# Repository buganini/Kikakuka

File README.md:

# Kikakuka — KiCad Workspace, Panelization, Build Variants, Differ & FreeCAD PCB Bending and Assembly

Kikakuka (企画課, きかくか, Planning Section) creates a few more dimensions for KiCad:

* Workspace and project management
* Revision management
* Build variants
* Panelization
* FreeCAD integration for flexible PCB bending and multi-board assembly

## Quick links

* [Features](#features)
* [Workspace Manager](#workspace-manager)
* [Schematic and PCB Differ](#differ)
* [PCB Build Variants](#fabrication-planner---build-variants)
* [PCB Panelization](#fabrication-planner---panelizer)
* [FreekiCAD Integration](#freekicad-freecad-addon)
* [Flexible PCB Bending](#flexible-pcb-bending)
* [Kikakuka KiCad Library](#kikakuka-library)
* [Technical Background and Evolution](#technical-background-and-evolution)
* [Run from source on Linux/macOS](#run-from-source-linuxmacos)
* [Run from source on Windows](#run-from-source-windows)
* [CLI Usage](#cli-usage)
* [Gerber-to-KiCad Conversion](#reverse-engineering-notes-for-kicad-gerber)

# Features
* Kikakuka main program
    * Workspace Manager
        * Organize KiCad projects, FabPlans, FreeCAD documents, assemblies, and STEP files in `.kkkk` workspaces with relative paths and file descriptions
        * Open related schematic, PCB, and STEP files or launch Differ and FabPlan from the workspace
        * Inspect project-specific symbol and footprint libraries and convert their paths to `${KIPRJMOD}`-relative references
    * Instance Manager UI
        * Inspect same-user KiCad and FreeCAD processes and known file paths, with one row per FreeCAD document, the matched KiCad IPC socket basename, automatic mesh-event updates, manual reconciliation, and Go to actions
    * Differ
        * Highlight changed areas
        * [Schematic diff viewer](#schematics-differ)
        * [PCB diff viewer](#pcb-differ)
        * Git support
    * Fabrication Planner
        * Panelizer
            * Interactive arrangement with real-time preview
            * Freeform placement not limited to M×N grid configurations
            * Support for multiple different PCBs in a single panel
            * Automatic or manual tab creation
            * Automatic V-cut/mousebites selection
            * Enable [hole](#substrate-hole) creation in panel substrate for extruded parts
            * Load [KiKit multiboard files](https://yaqwsx.github.io/KiKit/v1.8/multiboard/) as multiple separate boards
            * No coding skills required
        * Build Variants
            * Single PCB without panelization can be done with frameless setting
            * Each PCB can have its own flag settings
        * Reproducible workflows
            * Create and edit fabrication plans interactively in the GUI.
            * Save configurations in a portable, JSON-based `.kkkk_fab` file.
            * Generate outputs from the saved plan using either the GUI or CLI.
    * Gerber handling
        * Available in the fabrication planner (panelizer)
        * Or direct conversion to .kicad_pcb
        * Compared with KiCad output
            * Better restoration of oval drill holes
            * Allow attaching BOM/CPL (converted to [reference-only footprints](resources/kikakuka-internal.pretty/Footprint.kicad_mod))
    * CLI - Convert saved fabrication plans (`.kkkk_fab`, or legacy `.kikit_pnl`) to KiCad files in one command

* FreekiCAD (FreeCAD Addon)
    * Reloadable KiCad PCB Object
        * Optional copper and solder-mask import, with outer copper, inner copper, and mask controlled independently
        * Solid [stiffeners](#flexible-pcb-stiffener) from annotated `F.Stiffener` and `B.Stiffener` user-layer areas
        * [Flex PCB bending](#flexible-pcb-bending) driven by bend lines and parameters defined in KiCad
        * [Automatic coupler-based PCB alignment](#coupler-based-pcb-alignment) using matching `CouplerFixed` and `CouplerMoving` footprints or an absolute `CouplerAt`, with coupler plane markers for inspection
        * A sketch is provided for real-time board outline editing in FreeCAD
        * Components moved in FreeCAD are synced to KiCad in real time
    * Reloadable STEP/STL Object
    * Import and export assembly manifests (`.kkkk_asm`)
    * CLI - Export saved assembly manifests (`.kkkk_asm`) to STEP or STL in one command

* KiCad Plugin/Library
    * Coupler footprints for [Automatic coupler-based PCB alignment](#coupler-based-pcb-alignment)
    * Plugin actions for previewing and hiding coupler helpers in the 3D Viewer
    * Populate scaled placeholder 3D models for footprints without a valid model, using `SizeX`, `SizeY`, and `SizeZ` properties
        - Tutorial Video

* CADhoc / Instance Manager
    * Seamless navigation among Kikakuka, KiCad, and FreeCAD across multiple instances and open documents

# Workspace Manager
The `.kkkk` file saves workspace information in JSON format.
Adding or dropping a `.kicad_pcb` or `.kicad_sch` records its sibling
`.kicad_pro` project entry, even when that project file has not been created
yet. A virtual project row omits the `.kicad_pro` suffix; an existing project
file keeps it. Rows list only PCB/schematic files that currently exist.
Opening a missing project row reports the missing project instead of launching
KiCad.

# Differ
## Schematics Differ

## PCB Differ

* A diff sample of [cynthion-hardware](https://github.com/greatscottgadgets/cynthion-hardware)

# Fabrication Planner
The `.kkkk_fab` file saves panelization and build-variants settings in JSON format, with PCB paths stored relative to the file's location. Legacy `.kikit_pnl` files can still be opened or added; newly saved fabrication plans use `.kkkk_fab`.

# Fabrication Planner - Build Variants
Example: [`samples/build_variant.kkkk_fab`](samples/build_variant.kkkk_fab) and [`samples/build_variant.kicad_pcb`](samples/build_variant.kicad_pcb).

Set `BUILDEXPR` in footprints' properties. This can be done quickly with `Symbol Fields Table` using the current sheet only scope. Remember to sync them to PCB afterward.

* Kikakuka extracts build flags from `BUILDEXPR`. Selected flags are interpreted as true, and vice versa.
* Footprints with the BUILDEXPR evaluated as false will be marked as DNP.
* Footprints with unset or empty BUILDEXPR will be kept as is.

## BUILDEXPR
A boolean expression with operators:
* `~` Not
* `&` And
* `|` Or

It can be as simple as a build name as shown in the image above or an expression like `(A | ~B) & C`.

Panelization with different build variants

Single PCB without panelization can be done with frameless setting

## Field Values Variants
`Field#Flag` or multiple flags like `Field#FlagA#FlagB` will set `Field` to the value where build flags contain all the flags.

`Field#Opt=A`, `Field#Opt=B` will be displayed as dropdown options.

# Fabrication Planner - Panelizer
## Tutorial Video

[![
Kikakuka/FabPlanner – Panelization](https://img.youtube.com/vi/40IOZ7cjGgk/0.jpg)](https://www.youtube.com/watch?v=40IOZ7cjGgk)

<!--
## Global Alignment

## Per-PCB Alignment

-->

## Substrate Hole

### 3D Output

<!--
## Tight Frame + Auto Tab + V-Cuts *or* Mousebites

### Output

### 3D Output

## Tight Frame + Auto Tab + V-Cuts *and* Mousebites

## Loose Frame + Auto Tab + Mousebites

### 3D Output

## Auto Tab
Tab position candidates are determined by the PCB edge and max_tab_spacing, prioritized by divided edge length (smaller first), and skipped if there is a nearby candidate (distance < max_tab_spacing/3) with higher priority.

In the image below with debug mode on, small red dots are tab position candidates, larger red circles are selected candidates, and the two rectangles represent the two half-bridge tabs.

## Manual Tab
Auto tab is off for PCB with manual tabs.
Drag inside the PCB for moving selected tab, drag outside the PCB for changing the direction for the selected tab.

-->

# FreekiCAD (FreeCAD Addon)
Requires **FreeCAD 1.0** or later, **KiCad 9.0** or later,
`psutil>=7.2.2`, `kicad-python>=0.8,<0.9`, and `shapely>=2.0.7`. FreeCAD Addon
Manager may not automatically install packages where its allowed-package list
excludes them; install them manually inside FreeCAD if necessary. Installing
FreekiCAD from Kikakuka's Integration tab installs all three Python packages.

> [!NOTE]
> FreeCAD installed through Snap is not supported. Snap confinement isolates
> the filesystem and local sockets, preventing FreekiCAD from connecting to
> KiCad's IPC endpoint. Selecting the Snap executable manually does not remove
> this isolation; use a non-Snap FreeCAD installation or the official AppImage.
>

FreekiCAD and Kikakuka discover each other on demand through local Unix sockets
or Windows named pipes. FreeCAD can manage KiCad
instances without the Workspace Manager running. No board, assembly, or usage
data is sent to third parties.

When opening a FreeCAD file, Kikakuka first looks for an already open document
or reuses a responding FreeCAD instance; see
[CADhoc](cadhoc/README.md) for details.

KiCad `.kicad_pcb` boards and STEP models remain external files referenced by
path. When saved as `.FCStd`, the FreeCAD document caches their generated
objects and geometry, but the links remain reloadable from the source files. A
`.kkkk_asm` manifest stores source paths, settings, placements, and an optional
structured 3D viewport camera; it never contains cached objects or geometry.
Source paths are stored relative to the manifest whenever possible and resolved
from its directory on import, when every external source is loaded fresh. The
camera is restored field by field in FreeCAD's GUI, skipping unsupported or
invalid fields, and ignored by headless STEP/STL export.
`AutoReload` is enabled by default on both object types, so changing either
source file reloads its linked FreeCAD object. The option can be disabled
independently for each object.

> [!TIP]
> You can use Kikakuka's **Integration** tab to install, update, or uninstall the
> bundled KiCad plugin, KiCad library, and FreekiCAD addon. Close all instances
> of the affected application before using an install or uninstall button.
> Release builds already contain the addon packages. When running Kikakuka
> from source, generate them first with
> `python3 build-tools/build_addon_archives.py` (or
> `make archive-zips`); the GUI loads the resulting runtime packages from
> `build/addons/`.

For a standalone FreekiCAD deployment without Kikakuka, follow the
[FreekiCAD manual installation instructions](FreekiCAD/README.md#manual-installation).

* Activate `Preferences -> Plugins -> Enable KiCad API`. Kikakuka or FreekiCAD can reuse a running matching KiCad editor or start one on demand.
* FreekiCAD (FreeCAD Addon)
    * Add PCB
        * Drag and drop / Open / Import
            * Drag a `.kicad_pcb` file into FreeCAD, or use FreeCAD's Open or Import command; switching workbenches is not required.
        * FreekiCAD menu
            * Switch to the `FreekiCAD` workbench.
            * Menubar -> FreekiCAD -> Add KiCad PCB.
        * All of these entry points create the same linked PCB object.
        * The selected `.kicad_pcb` remains an external file and is represented by a linked `PcbObject`. Its `AutoReload` property defaults to enabled.
    * Add STEP
        * Menubar -> FreekiCAD -> Add STEP
        * The selected STEP model remains an external file. Its `AutoReload` property defaults to enabled, and its Placement is preserved when the source file is manually or automatically reloaded.
    * Position and assemble linked objects
        * Linked objects work with the `Assembly` and `Manipulator` workbenches, as well as FreeCAD's built-in transform tool.
        * FreeCAD Assembly can place `PcbObject` Links, but currently cannot resolve their child component or connector faces for joints. Use the Manipulator workbench to align those faces.
    * Reload PCB
        * Right-click on the board object -> Reload KiCad PCB
    * Export or import an assembly manifest
        * Use FreeCAD's standard Export command to write `.kkkk_asm`, or its Import command to read `.kkkk_asm`; select `FreekiCAD Assembly (*.kkkk_asm)` as the file type.
        * The JSON stores each external PCB or STEP source path, editable FreekiCAD settings, its placement, and—when exported from the GUI—the active 3D viewport camera. It contains no cached objects or generated geometry, and every external source is loaded fresh during import. Export prefers paths relative to the manifest and falls back to absolute paths only when necessary; relative paths are resolved from the manifest's directory. FreeCAD regenerates object names and labels during import. GUI import restores each available camera field independently after recomputation and skips fields that are invalid or unsupported; headless STEP/STL export ignores the camera.
        * Selecting an original `PcbObject` or `StepObject` exports its own Placement. Selecting one or more `App::Link` instances exports each linked source at that instance's final global placement. Selecting an `Assembly::AssemblyObject` recursively expands its direct and nested Links, including multiple instances of the same source.
        * Assembly and Link exports are flattened placement snapshots; `.kkkk_asm` does not store Links, joints, constraints, remaining degrees of freedom, or the Assembly hierarchy. A linked PCB snapshot is exported with `SnapToCoupler` disabled in the manifest so coupler alignment cannot overwrite its solved Assembly placement; the source `PcbObject` in the current FreeCAD document is not modified.
        * When original PCB source objects are selected directly, Placement is omitted for a `CouplerMoving` board if the same export contains its matching `CouplerFixed` board; coupler alignment recalculates that placement after import.
        * Headless STEP export: `freecadcmd scripts/kkkk_export.py input.kkkk_asm output.step`; the input may also be a single `.kicad_pcb`. See [Headless STEP and STL Export](FreekiCAD/README.md#headless-step-and-stl-export) for platform-specific paths and requirements.
    * Edit Board Shape
        * Expand the object's children.
        * Open the sketch with the `_Outline` suffix.
    * Inspect Copper Layers
        * FreekiCAD imports tracks, filled zones, pads, vias, and copper-layer graphics as separate `F.Cu`, `In*.Cu`, and `B.Cu` child objects.
        * `ImportOuterCopper` independently controls `F.Cu` and `B.Cu`; `ImportInnerCopper` controls `In*.Cu`. Both default to off.
        * Inner layers use their physical stackup Z and are normally hidden by the board body; hide the board or make it transparent to inspect them.
        * Copper is rendered as one unioned zero-thickness face per layer, eliminating overlap between tracks, pads, vias, and zones. Each face retains its physical stackup Z, so inner layers follow the correct bend radius.
        * The substrate remains one body. Imported outer copper reserves its physical stackup thickness at the body boundary; inner copper does not create expensive internal body cavities. Finished board thickness and component/coupler Z never change.
    * Inspect Solder Mask
        * `ImportSolderMask` imports translucent `F.Mask` and `B.Mask` child objects, with pad/via openings computed by KiCad plus explicit mask-layer graphics. It defaults to off.
        * The resulting F/B mask-opening geometry is also subtracted from stiffener solids on the matching side.
        * With mask import enabled, the board body uses the configured dielectric stackup colors and KiCad opacity, or white with KiCad's default board-body opacity when no color is available. Mask opacity likewise follows its KiCad stackup color. Both display opacities are scaled to 70% in FreeCAD. With mask import disabled, the original opaque board color is preserved.
        * Mask is a zero-thickness face at the finished outer surface. Imported mask reserves its physical outer stackup thickness in the single substrate body; when mask import is disabled, the body fills that thickness.
    * Inspect Silkscreen
        * `ImportSilkscreen` imports board- and footprint-level graphics, references, values, fields, and free text from `F.SilkS` and `B.SilkS`. It defaults to off.
        * Silkscreen is a zero-thickness face on the finished board surface. A Coin3D polygon offset resolves viewport z-fighting without moving the geometry, so measurements, bounds, and exports retain the exact finished dimensions.
    * [Flexible PCB Stiffener](#flexible-pcb-stiffener)
        * Import annotated stiffener solids automatically from `F.Stiffener` and `B.Stiffener` user layers.
    * [Coupler-Based PCB Alignment](#coupler-based-pcb-alignment)
        * Place a `CouplerFixed` footprint on the reference PCB and a `CouplerMoving` footprint on the PCB to be aligned. Couplers are matched by their KiCad reference.
        * Alternatively, place one `CouplerAt` on a PCB to align it with a virtual `CouplerFixed` at the absolute FreeCAD world coordinates given by its `TargetX`, `TargetY`, and `TargetZ` properties. All three default to `0 mm`. Usually place `CouplerAt` on B.Cu so the PCB bottom surface is positioned at `TargetZ`; use F.Cu only when the top surface should be the reference. A PCB may contain only one positioning source: one `CouplerMoving` or one `CouplerAt`.
        * After any linked PCB reloads, positioning is recalculated for every linked PCB in dependency order. A concurrently reloading PCB is skipped until its fresh poses and bent markers are available; its completion triggers another full pass. A PCB with `SnapToCoupler` enabled (the default) is moved as a whole so that its moving coupler plane meets the matching fixed coupler plane face-to-face; disabling it excludes that PCB from automatic positioning. Alignment uses each plane's position after flex-PCB bending. Each coupler is also available as a child object in FreeCAD; its plane marker is hidden by default and can be shown for inspection.
        * FreekiCAD checks the saved coupler list against KiCad's live document every second, including unsaved position, side, rotation, `Z`, `Offset`, `Tilt`, and `CouplerAt` target edits. A changed pose updates its marker and recalculates linked-board positioning. The coupler child object's footprint position and local-plane properties are editable in FreeCAD; edits update the marker and linked-board positioning immediately and are written back to the live KiCad footprint. `Y` is shown using FreeCAD's axis convention. Older footprints without an `Offset` field load as `0 mm`; editing `Offset` in FreeCAD creates the missing hidden KiCad field automatically. Adding, removing, or changing the identity of couplers takes effect on the next PCB reload, which rebuilds the saved list.
        * The [`kicad-addon/library`](kicad-addon/library) directory provides [`CouplerFixed`](kicad-addon/library/footprints/Kikakuka.pretty/CouplerFixed.kicad_mod), [`CouplerMoving`](kicad-addon/library/footprints/Kikakuka.pretty/CouplerMoving.kicad_mod), and [`CouplerAt`](kicad-addon/library/footprints/Kikakuka.pretty/CouplerAt.kicad_mod).
        * Alignment example boards: [`assembly-power.kicad_pcb`](samples/assembly-power.kicad_pcb), [`assembly-mcu.kicad_pcb`](samples/assembly-mcu.kicad_pcb), [`assembly-led.kicad_pcb`](samples/assembly-led.kicad_pcb), and [`assembly-mezzanine.kicad_pcb`](samples/assembly-mezzanine.kicad_pcb).
        * The coupler plane is defined by the footprint position, side, rotation, and these custom footprint properties:
            * `CouplerFixed` and `CouplerMoving` use `Z` to move the plane origin along the PCB surface normal. It defaults to `0 mm`; the origin starts at the PCB surface, including the board thickness on F.Cu, and the direction is reversed on B.Cu.
            * `Offset` moves the plane origin on the PCB surface in the direction indicated by the footprint triangle. It defaults to `0 mm`. `Z` and `Offset` accept values without a unit as millimetres and support `mm`, `cm`, `in`, `mil` (`0.001 in`), and `um`.
            * `Tilt` tilts the plane around the footprint's local X axis. It is specified in degrees and defaults to `0`.
            * `CouplerAt` uses `TargetX`, `TargetY`, and `TargetZ` as its absolute FreeCAD world target and does not have a local `Z` property. The target properties default to `0 mm`; the same length units are supported. B.Cu is recommended for the usual bottom-surface placement at `TargetZ`; use F.Cu only to reference the top surface.
        * Placement applies the footprint position and rotation, then `Offset`, `Z`, and `Tilt`. `Tilt` rotates around the footprint's local X axis at the offset origin; it does not redirect either displacement. The footprint's normal KiCad rotation supplies the rotation around its local Z axis.
    * [Flex PCB Bending](#flexible-pcb-bending)
        * Name a KiCad graphical layer `FreekiCAD` (case-insensitive) and draw bend lines on it as line segments.
        * Panel export maps every source PCB's `FreekiCAD` drawings to one collision-free User layer and preserves the `freekicad` layer name, even when source boards use different `User.x` layers.
        * Add bend parameters as text on the same `FreekiCAD` layer near a bend line endpoint, for example `a=-70 r=0.5` or `a=-70 s=0.61`.
            * The text anchor must be within `0.1 mm` of a bend line endpoint.
            * `a` is bend angle in degrees.
            * `r` is bend radius. `s` is the full bend span and is used to derive `r` when `r` is omitted, using the board thickness from stackup.
            * Both lengths accept `mm`, `cm`, `um` (also `µm`/`μm`), `in`, and `mil`; omitted units mean mm. Unit suffixes are case-insensitive. Unsupported units are rejected.
            * Parameters may appear in any order, with whitespace around `=` and before units: `r = 5 mm a = 60` is equivalent to `a=60 r=5mm`. If both `r` and `s` are present, `r` takes precedence.
        * After loading the board in FreeCAD, each bend line appears as a child object with `Angle`, `Radius`, and `Active` properties.
        * The linked PCB object also has an `EnableBending` property to toggle the deformation on or off.
        * Imported copper and solder mask are cut with the same board pieces. Rigid display faces follow each piece, while faces in a bend band are rebuilt with the wedge's curved point mapping.
        * If no bend text is provided, the bend line still loads and can be configured directly in FreeCAD.

## Coupler-Based PCB Alignment

### Tutorial Video

### Positioning Arguments

### Coupler Pair

### Changing Z and Tilt

Coupler plane markers are available as child objects in FreeCAD and are hidden by default.

## Flexible PCB Stiffener

Rename KiCad user layers to `F.Stiffener` and/or `B.Stiffener`
(case-insensitive). Each closed rectangle, circle, polygon, or connected
line/arc outline is imported automatically as one stiffener area; the KiCad
display fill may be on or off.
Put one text annotation inside each area and separate properties with `/` or
newlines:

```text
Name=Tail reinforcement
Material=Polyimide
Color=#C87518
Opacity=0.65
Thickness=25 um
```

`Material` and `Thickness` are required. `Name`, `Color`, and `Opacity` are
optional and property names are case-insensitive. A non-empty `Name` becomes
the suffix of the FreeCAD child name and label (`F_Stiffener_<Name>` or
`B_Stiffener_<Name>`) and is included in bend-overlap warnings. Thickness
accepts `mm`, `cm`, `in`, `mil` (`0.001 in`), and `um`; a unitless value is
interpreted as millimetres.

Invalid annotations, annotations outside an area, and areas with multiple
annotations are reported as errors and skipped. Unannotated areas are skipped
with a warning.

| Material | Default color | Default opacity |
| --- | --- | ---: |
| `FR4` | `#C8B45A` | `0.90` |
| `Polyimide` | `#C87518` | `0.65` |
| `Stainless_Steel` | `#A7ADB4` | `1.00` |
| `3M468` | `#F2E3BD` | `0.28` |
| `tesa8854` | `#EEE8D8` | `0.45` |
| `3M9077` | `#DDE8EE` | `0.30` |

Other material names are accepted with a warning. When `Color` or `Opacity`
is omitted for an unlisted material, the corresponding `Polyimide` default is
used.

Front stiffeners extend outward from the front silkscreen plane; back
stiffeners extend outward from the back silkscreen plane. They remain rigid
during flex bending. Pad, via, and explicit mask-graphic openings on `F.Mask`
are cut through front stiffeners; `B.Mask` openings are cut through back
stiffeners. This happens even when `ImportSolderMask` is disabled. If a
stiffener overlaps the full bend band, FreekiCAD prints a warning containing
the stiffener name, bend name, and overlap area.

Stiffener thickness is additive outside the finished PCB and is never counted
in or subtracted from the board body.

## Flexible PCB Bending
### Tutorial Video

Manual bending checks are currently done with these sample boards:

* [`samples/fpc.kicad_pcb`](samples/fpc.kicad_pcb)
* [`samples/maze.kicad_pcb`](samples/maze.kicad_pcb)
* [`samples/maze_radius.kicad_pcb`](samples/maze_radius.kicad_pcb)

<!--

-->

For the implementation details of the bending pipeline, see [`FreekiCAD/ARCHITECTURE.md`](FreekiCAD/ARCHITECTURE.md).

### Bending + Assembly

# Kikakuka Library
The KiCad library is stored under [`kicad-addon/library`](kicad-addon/library).
You can install it from Kikakuka's **Integration** tab. For a manual installation,
add [`kicad-addon/library/footprints/Kikakuka.pretty`](kicad-addon/library/footprints/Kikakuka.pretty)
to KiCad's footprint library table (for example, as `Kikakuka`). Its
[`Kikakuka.3dshapes`](kicad-addon/library/3dmodels/Kikakuka.3dshapes) directory
contains the unit-cube placeholder and optional coupler helper models.

* [`Variable`](kicad-addon/library/footprints/Kikakuka.pretty/Variable.kicad_mod) displays its `Value` on the board. In the Kikakuka Fabrication Planner, use build-variant fields such as `Value#Flag` or `Value#Option=Choice` to show a value selected by the active build flags or options.
* [`StringTemplate`](kicad-addon/library/footprints/Kikakuka.pretty/StringTemplate.kicad_mod) formats its `Value` during Kikakuka Fabrication Planner export. Braced placeholders are replaced with matching footprint properties or build options after build-variant fields have been applied.
* [`CouplerFixed`](kicad-addon/library/footprints/Kikakuka.pretty/CouplerFixed.kicad_mod) and [`CouplerMoving`](kicad-addon/library/footprints/Kikakuka.pretty/CouplerMoving.kicad_mod) define matching planes for [coupler-based PCB alignment](#coupler-based-pcb-alignment). Give a pair the same reference and use their `Z`, `Offset`, and `Tilt` properties as needed.
* [`CouplerAt`](kicad-addon/library/footprints/Kikakuka.pretty/CouplerAt.kicad_mod) aligns its PCB to absolute FreeCAD world `TargetX`, `TargetY`, and `TargetZ` coordinates, all defaulting to zero. Place it on B.Cu for the usual behavior, where the PCB bottom surface is positioned at `TargetZ`; use F.Cu only to reference the top surface.

For coupler length properties (`Z`, `Offset`, `TargetX`, `TargetY`, and `TargetZ`), unitless values are millimetres; supported suffixes are `mm`, `cm`, `in`, `mil`, and `um`/`µm`. `Tilt` is in degrees and may optionally use `deg` or `°`.

All three coupler footprints use the `Unspecified` type, placing their helper models under **Virtual Models** in KiCad's 3D Viewer.

The separate Kikakuka Tools IPC plugin provides **Coupler 3D Viewer** and **Hide Couplers** actions. Coupler 3D Viewer applies each coupler's `Z`, `Tilt`, and `Offset` to its helper model and opens KiCad's 3D Viewer; Hide Couplers marks these models hidden without removing them and also opens the Viewer. **Populate Placeholder 3D Models** likewise opens the Viewer after populating models. To omit couplers from STEP export, enable **Ignore 'Unspecified' components**.

# Technical Background and Evolution
Kikakuka is mainly built on top of [KiKit](https://github.com/yaqwsx/KiKit), [Shapely](https://github.com/shapely/shapely), modified [pcb-tools](https://github.com/curtacircuitos/pcb-tools), [OpenCV](https://github.com/opencv/opencv-python), [pypdfium2](https://github.com/pypdfium2-team/pypdfium2) and [PUI](https://github.com/buganini/PUI).

Its FreeCAD integration is inspired by [KiCadStepUp](https://github.com/easyw/kicadStepUpMod) and [KiConnect](https://codeberg.org/kiconnect/KiConnect).

Kikakuka, formerly Kikit-UI, began as an interactive GUI for KiKit and later expanded to include a workspace manager. File-to-instance tracking was introduced to make navigation from the workspace manager to KiCad reliable, with the workspace manager initially serving as the central orchestrator. After FreekiCAD was introduced, that mechanism evolved into CADhoc, a mesh of peer nodes running in Kikakuka and FreekiCAD without a permanent central orchestrator. The mesh also includes a client-only node in the KiCad add-on. CADhoc maintains a shared view of KiCad and FreeCAD instances and their open documents, so navigation no longer depends on the workspace manager.

# Run from source (Linux/macOS)
Make sure your python can import `pcbnew`
```
> python3 -c "import pcbnew; print(pcbnew._pcbnew)"
<module '_pcbnew' from '/usr/lib/python3/dist-packages/_pcbnew.so'>
```
On macOS, I have to use the python interpreter bundled with KiCAD
```
PYTHON=/Applications/KiCad/KiCad.app/Contents/Frameworks/Python.framework/Versions/Current/bin/python3
```

On Linux, you should be able to just use the your default python3
```
PYTHON=python3
```

Create a virtual environment and install dependencies
```
${PYTHON} -m venv --system-site-packages env
./env/bin/pip3 install -r requirements.txt
```

On Debian/Ubuntu, PySide6's X11 platform plugin also needs these system libraries:
```
sudo apt install libxcb-cursor0 libxkbcommon-x11-0 libxcb-icccm4 libxcb-image0 libxcb-keysyms1 libxcb-render-util0 libxcb-xkb1
```

Kikakuka uses `opencv-python-headless` for image processing and PySide6 for its
windows. If an existing environment has `opencv-python` installed, replace it
before reinstalling requirements (both packages provide the same `cv2` module):
```
./env/bin/pip3 uninstall opencv-python
./env/bin/pip3 install -r requirements.txt
```

Update submodule
```
git submodule update --init --recursive
```

Run
```
./env/bin/python3 -m kikakuka
# Equivalent directory entry point:
./env/bin/python3 kikakuka/
```

# Run from source (Windows)
On Windows the Python interpreter is at `C:\Program Files\KiCad\10.0\bin\python.exe`.
But however in my Windows environment venv is not working properly, here is how I run it with everything installed in the KiCad's environment.
``` powershell
# Powershell
# Initialize bundled submodules after cloning
git submodule update --init --recursive

# Git for Windows may check symlinks out as text files containing their target
# paths. Replace all tracked symlinks with physical files/directories so the
# source tree can run without Windows symlink support.
& .\tools\materialize-symlinks.ps1

&"C:\Program Files\KiCad\10.0\bin\python.exe" -m pip install -r requirements.txt
&"C:\Program Files\KiCad\10.0\bin\python.exe" -m kikakuka
```

The materialization only changes the working tree; Git still tracks those paths
as symlinks. Re-running the script refreshes the physical copies. If PowerShell
blocks local scripts, run
`powershell -ExecutionPolicy Bypass -File .\tools\materialize-symlinks.ps1`.

# CLI Usage
```
# Just open it
./env/bin/python3 -m kikakuka

# Start with PCB files
./env/bin/python3 -m kikakuka a.kicad_pcb b.kicad_pcb...

# Open KiCad files through the instance manager
./env/bin/python3 -m kikakuka --open a.kicad_pcb

# Run a foreground CADhoc node with request/mapping logs
./env/bin/python3 -m cadhoc
# The equivalent directory entry point is: ./env/bin/python3 cadhoc

# Open or focus a PCB and reload it from disk once its IPC API is ready
./env/bin/python3 -m kikakuka --open --fresh a.kicad_pcb
# In a mixed list, --fresh affects only .kicad_pcb files; schematics and
# projects are opened normally.

# Stop all same-user KiCad and FreeCAD GUI instances (not FreeCADCmd)
# Warning: unsaved work may be lost.
./env/bin/python3 -m kikakuka --killall

# Stop only one application (case-insensitive)
./env/bin/python3 -m kikakuka --killall freecad
./env/bin/python3 -m kikakuka --killall kicad

# Export a FreekiCAD assembly through the detected FreeCADCmd and bundled exporter
./env/bin/python3 -m kikakuka input.kkkk_asm output.step
./env/bin/python3 -m kikakuka input.kkkk_asm output.stp
./env/bin/python3 -m kikakuka input.kkkk_asm output.stl

# Run the detected FreeCADCmd with pass-through arguments
./env/bin/python3 -m kikakuka --freecadcmd FreekiCAD/scripts/kkkk_export.py input.kkkk_asm output.step

# Load file (.kkkk, .kkkk_fab, or legacy .kikit_pnl)
./env/bin/python3 -m kikakuka a.kkkk_fab

# Headless export for panelization or build variants
./env/bin/python3 -m kikakuka a.kkkk_fab out.kicad_pcb

# Differ
./env/bin/python3 -m kikakuka --differ a.kicad_sch b.kicad_sch
./env/bin/python3 -m kikakuka --differ a.kicad_pcb gerber_folder
./env/bin/python3 -m kikakuka --differ gerber.zip b.kicad_pcb

# Gerber to KiCAD Conversion
./env/bin/python3 -m kikakuka gerber.gbr out.kicad_pcb
./env/bin/python3 -m kikakuka gerber_folder out.kicad_pcb # BOM/CPL will be detected if they are in the folder
./env/bin/python3 -m kikakuka gerber.zip out.kicad_pcb
./env/bin/python3 -m kikakuka gerber.zip out.kicad_pcb bom_or_cpl_1.csv bom_or_cpl_2.csv # BOM/CPL files are determined by filename regardless of argument order
```

# Reverse-Engineering Notes for KiCAD Gerber
* Convert Gerber to .kicad_pcb with BOM/CPL using `Kikakuka`
* Footprint names are also exported, so `Tools -> Update Footprints from Library` can bring back the footprint if the name matches
* Lock the footprint, clean up with quick selection and deletion, unlock the footprint (you will need to set the `Selection Filter`)

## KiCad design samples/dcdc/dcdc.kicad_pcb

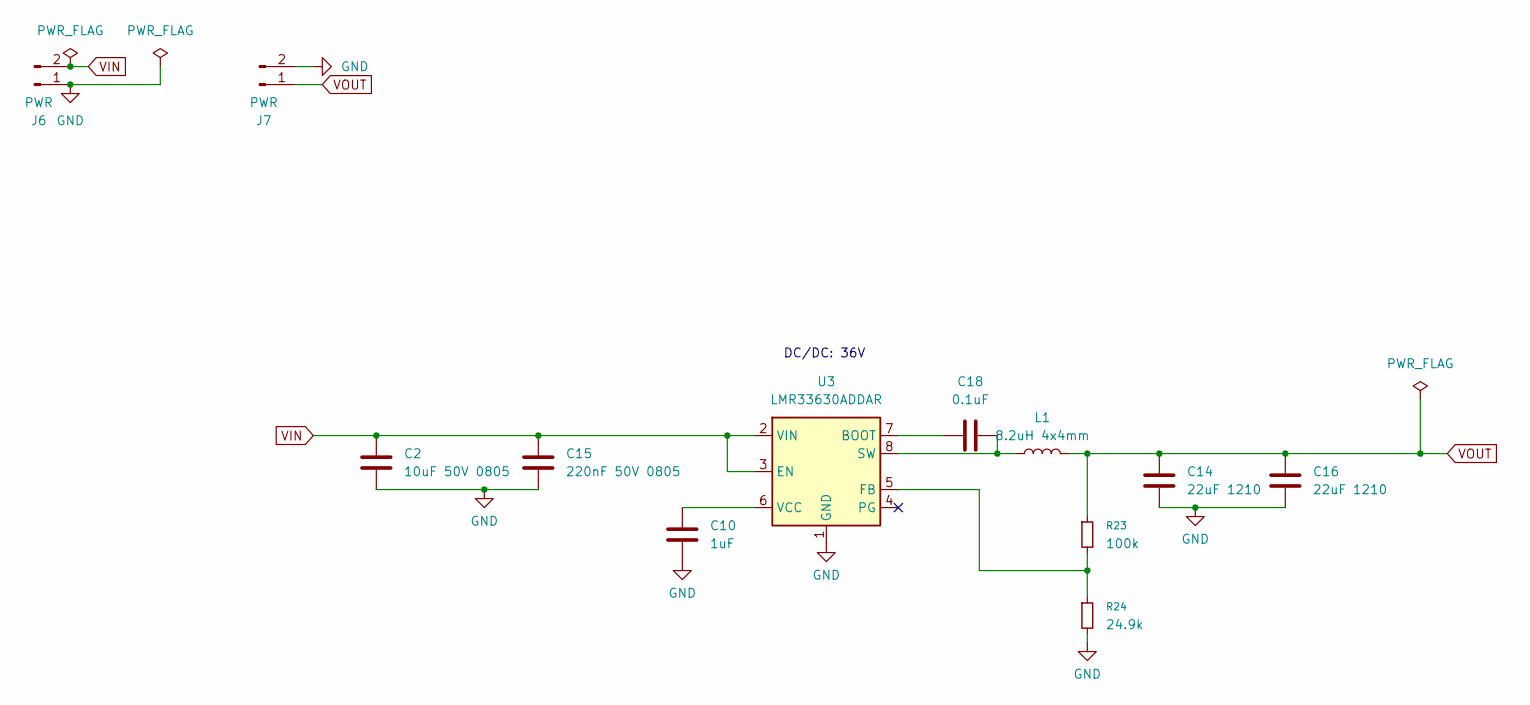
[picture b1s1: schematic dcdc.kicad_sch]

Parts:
C2: 10uF 50V 0805; C_0805_2012Metric; LCSC C440198
C10: 1uF; C_0603_1608Metric; LCSC C15849
C14, C16: 22uF 1210; C_1210_3225Metric; LCSC C19659
C15: 220nF 50V 0805; C_0805_2012Metric; LCSC C5378
C18: 0.1uF; C_0603_1608Metric; LCSC C14663
J6, J7: PWR; TerminalBlock_Phoenix_PT-1,5-2-5.0-H_1x02_P5.00mm_Horizontal; LCSC C474881
L1: 8.2uH 4x4mm; L_Changjiang_FNR4030S; LCSC C167878
R23: 100k; R_0603_1608Metric; LCSC C25803
R24: 24.9k; R_0603_1608Metric; LCSC C25962
U3: LMR33630ADDAR; Texas_HSOP-8-1EP_3.9x4.9mm_P1.27mm_ThermalVias; LCSC C841384

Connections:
GND: C2.1, C10.1, C14.2, C15.1, C16.2, J6.1, J7.2, R24.2, U3.1 (GND), U3.9 (GND)
unnamed: C18.2, U3.7 (BOOT)
unnamed: R23.2, R24.1, U3.5 (FB)
unnamed: C18.1, L1.1, U3.8 (SW)
unnamed: C10.2, U3.6 (VCC)
VIN: C2.2, C15.2, J6.2, U3.2 (VIN), U3.3 (EN)
VOUT: C14.1, C16.1, J7.1, L1.2, R23.1

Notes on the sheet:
DC/DC: 36V

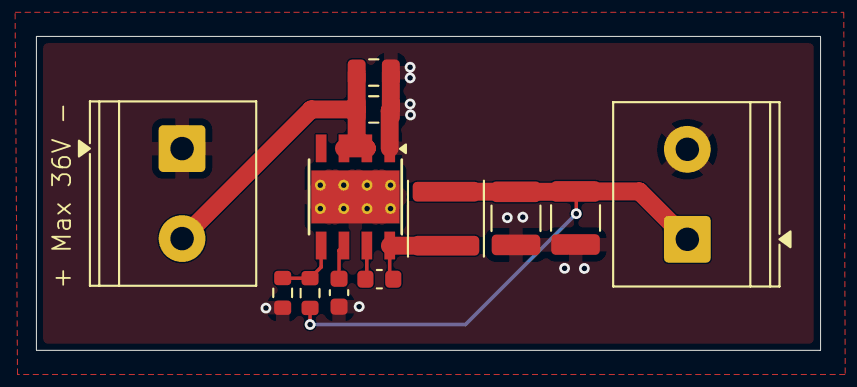
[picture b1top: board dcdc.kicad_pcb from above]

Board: 4 copper layers, 43.6 x 17.4 mm, 12 parts (0 on the bottom side), 7 nets.

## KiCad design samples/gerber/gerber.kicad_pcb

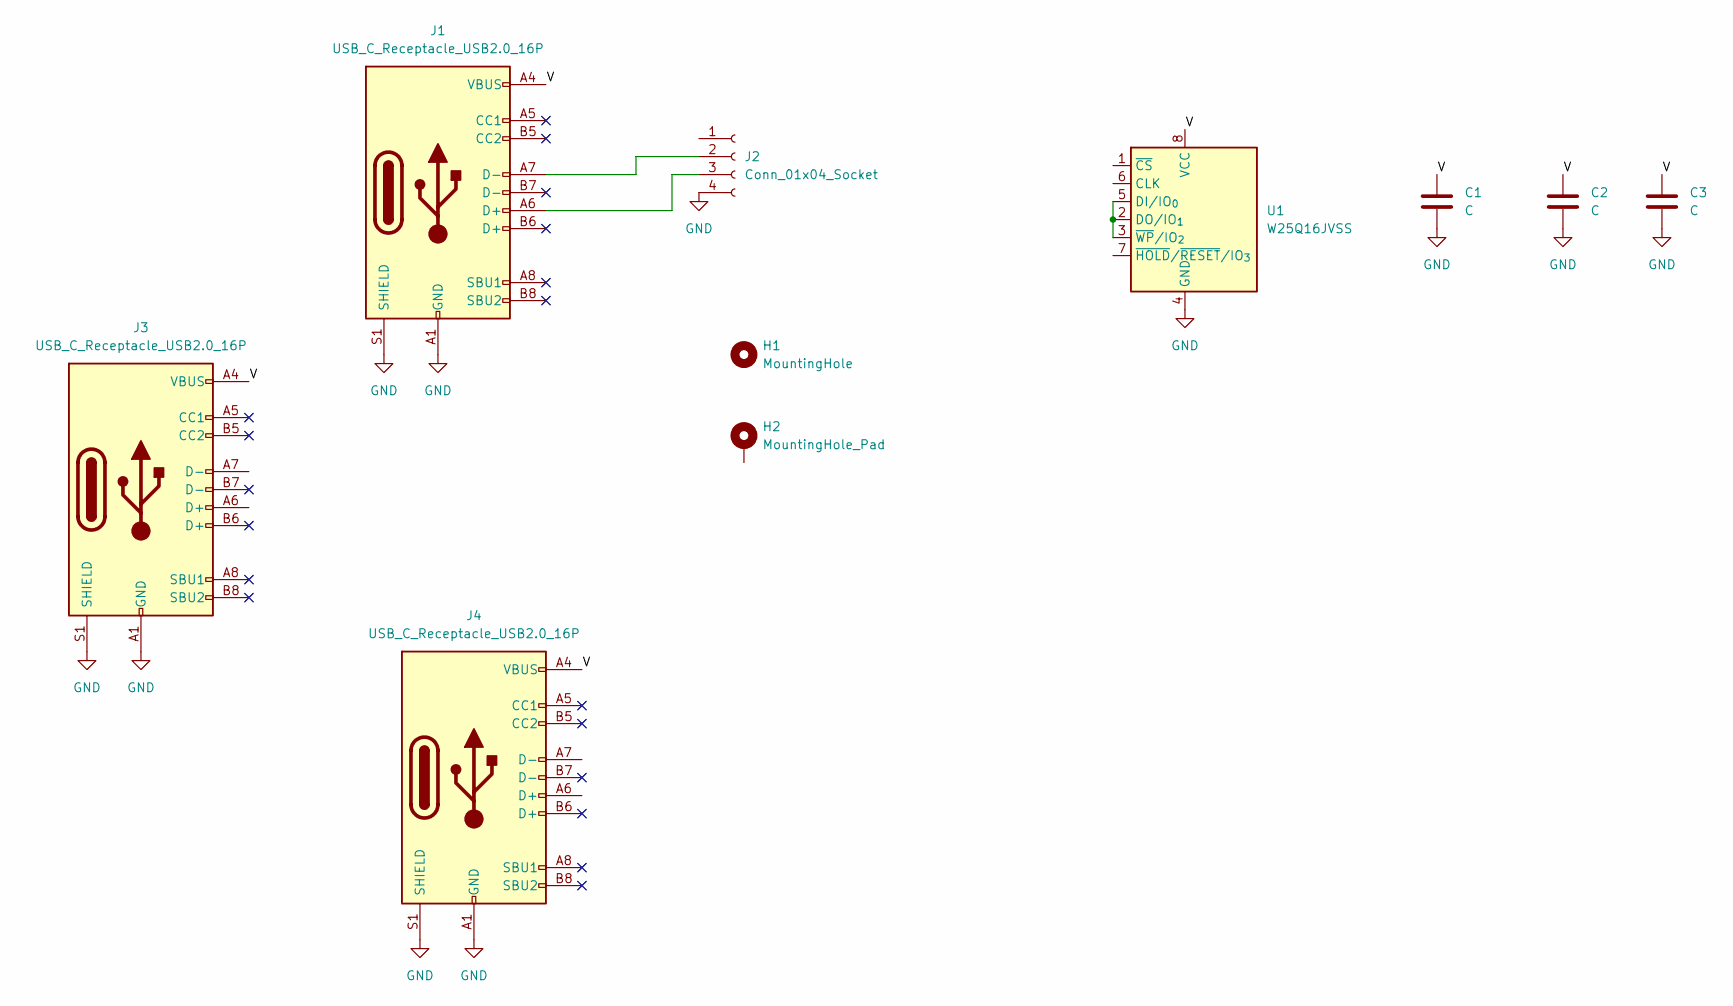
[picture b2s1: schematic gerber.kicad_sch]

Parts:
C1: C; C_0402_1005Metric
C2, C3: C; C_1210_3225Metric
H1: MountingHole; MountingHole_3.2mm_M3
H2: MountingHole_Pad; MountingHole_3.2mm_M3_Pad
J1, J3, J4: USB_C_Receptacle_USB2.0_16P; USB_C_Receptacle_G-Switch_GT-USB-7051x; LCSC C2843970
J2: Conn_01x04_Socket; PinHeader_1x04_P2.54mm_Vertical
U1: W25Q16JVSS; SOIC-8_5.3x5.3mm_P1.27mm

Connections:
/V: C1.1, C2.1, C3.1, J1.A4 (VBUS), J1.A9 (VBUS), J1.B4 (VBUS), J1.B9 (VBUS), J3.A4 (VBUS), J3.A9 (VBUS), J3.B4 (VBUS), J3.B9 (VBUS), J4.A4 (VBUS), J4.A9 (VBUS), J4.B4 (VBUS), J4.B9 (VBUS), U1.8 (VCC)
GND: C1.2, C2.2, C3.2, J1.A1 (GND), J1.A12 (GND), J1.B1 (GND), J1.B12 (GND), J1.S1 (SHIELD), J2.4, J3.A1 (GND), J3.A12 (GND), J3.B1 (GND), J3.B12 (GND), J3.S1 (SHIELD), J4.A1 (GND), J4.A12 (GND), J4.B1 (GND), J4.B12 (GND), J4.S1 (SHIELD), U1.4 (GND)
unnamed: J1.A7 (D-), J2.2
unnamed: J1.A6 (D+), J2.3
unnamed: U1.2 (DO/IO_{1}), U1.3 (~WP/IO_{2}), U1.5 (DI/IO_{0})

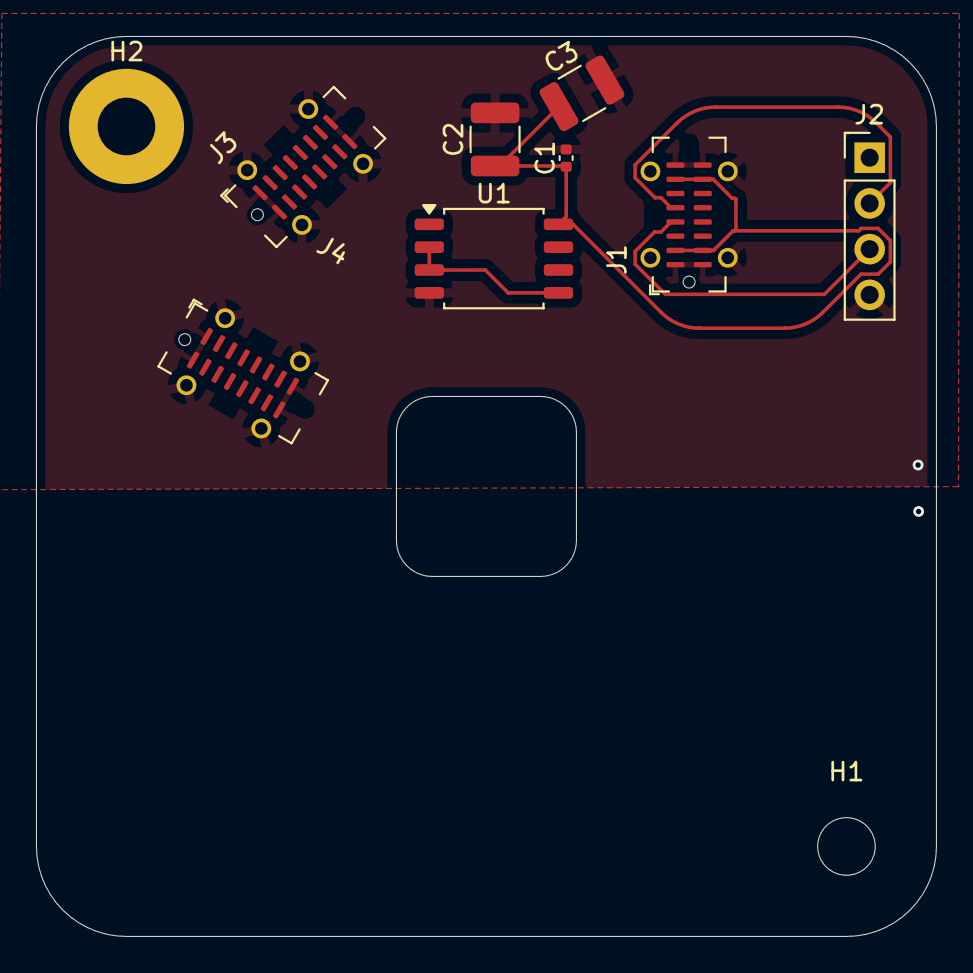
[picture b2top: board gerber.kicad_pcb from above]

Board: 2 copper layers, 50.0 x 50.0 mm, 10 parts (0 on the bottom side), 5 nets.

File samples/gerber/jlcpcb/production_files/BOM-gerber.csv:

Comment,Designator,Footprint,LCSC,Quantity
USB_C_Receptacle_USB2.0_16P,"J1,J3,J4",USB_C_Receptacle_G-Switch_GT-USB-7051x,C2843970,3
Conn_01x04_Socket,J2,PinHeader_1x04_P2.54mm_Vertical,,1
W25Q16JVSS,U1,SOIC-8_5.3x5.3mm_P1.27mm,,1
C,C2,C_1210_3225Metric,,1
C,C3,C_1210_3225Metric,,1
C,C1,C_0402_1005Metric,,1

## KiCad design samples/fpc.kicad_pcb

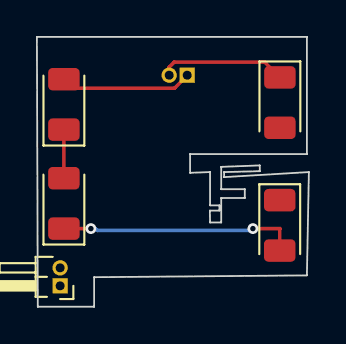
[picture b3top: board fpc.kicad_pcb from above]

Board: 2 copper layers, 15.1 x 15.0 mm, 7 parts (1 on the bottom side), 5 nets.

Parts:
D1, D2, D3, D4: IR26-21C_L110_TR8; LED_1206_3216Metric
J1, J2: Conn_01x02_Pin; PinHeader_1x02_P1.00mm_Horizontal
conn: CouplerFixed

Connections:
unnamed: D1.2 (A), D2.1 (K)
unnamed: D1.1 (K), J1.2
unnamed: D2.2 (A), D3.1 (K)
unnamed: D3.2 (A), D4.1 (K)
unnamed: D4.2 (A), J1.1

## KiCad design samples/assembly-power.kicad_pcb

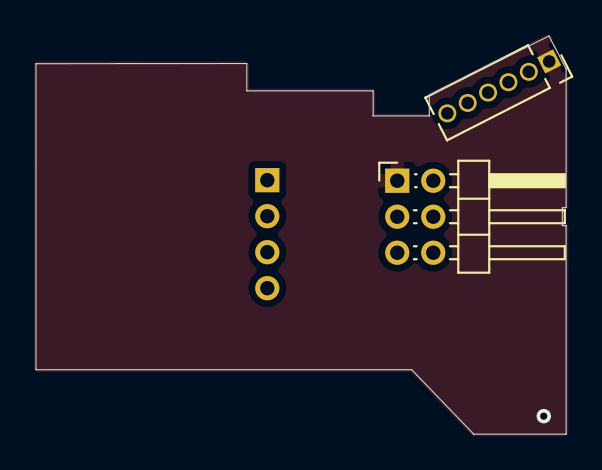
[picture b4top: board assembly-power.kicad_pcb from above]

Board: 4 copper layers, 29.4 x 22.1 mm, 5 parts (1 on the bottom side), 6 nets, no tracks yet.

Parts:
J2: Conn_01x06_Pin; PinHeader_2x03_P2.00mm_Horizontal
J3: Conn_01x06_Socket; PinSocket_1x06_P1.27mm_Vertical
led: CouplerFixed
mcu: CouplerFixed
mezzanine: CouplerFixed

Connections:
/12V: J2.2, J3.2
GND: J2.1, J3.1
PWM_CH1: J2.6, J3.3
PWM_CH2: J2.4, J3.4
PWM_CH3: J2.3, J3.5
PWM_CH4: J2.5, J3.6
